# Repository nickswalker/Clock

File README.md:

Tock
====

An Arduino based nightstand alarm clock.

* Multiple alarms
* Accurate time with battery backup
* Configurable over Bluetooth Low Energy with [Tick](https://github.com/nickswalker/tick)

Independent Study Mentorship project for senior year at Communications Arts High School (2014).

### Hardware

The Tock is built around an Arduino-compatible board which is meant to be used in conjunction with a number
of cheap, widely available supporting modules. The PCB exposes all of the pins of the microcontroller, 
so it's easy to extend.

#### Bill of Materials

Part (Digi-Key #) | Quantity |
:---------------- | :-------:|
[Project PCB]()   | 1  
[HM-10 module](http://www.fasttech.com/products/0/10004051/1292002-ti-cc2540-bluetooth-40-ble-2540-transparent-serial) | 1
[Real time clock module]() | 1
[Adafruit I2C 4 digit seven segment display]() | 1
[Photoresistor]() | 1
[Female to male jumpers]() | 12
[Male header]()   | 2 rows of 40
[Female header]() | 1 row of 40
              | 1

### Firmware

The C++ Arduino sketch uses three main global singletons to manage the hardware; an `IOHandler`, a 
`TimeKeeper` and `SensorHandler`. Hardware extensions should be coupled with additional methods on
these objects. Another singleton, the `AlarmsManager`, handles the interpretation of time events. A 
`Settings` class exposes methods to manipulate the EPROM for storing information between power cycles.

Various subclasses of the abstract `Command` class encapsulate the interpretation and execution of
commands recieved over the UART line from the Bluetooth Low Energy module. The `Command` class itself
contains a factory method for producing its concrete subclasses. Each of these has full access to the 
global singletons and can manipulate the state of the clock.

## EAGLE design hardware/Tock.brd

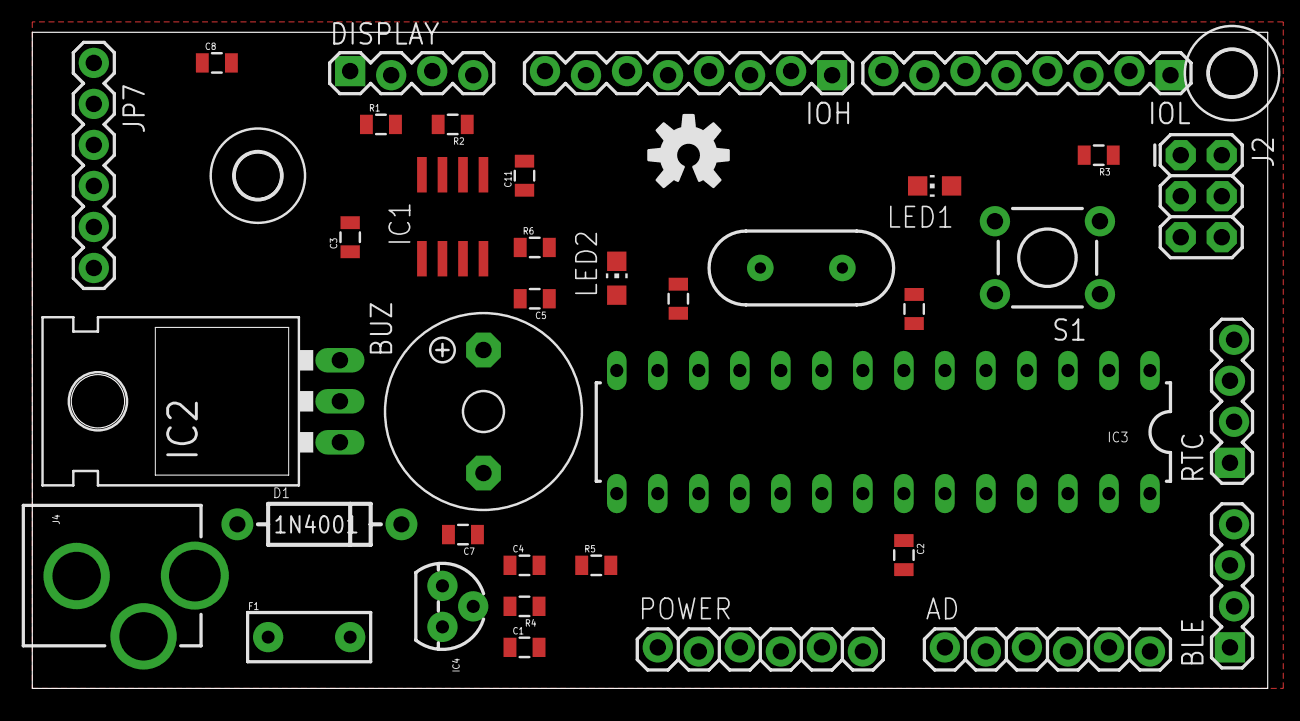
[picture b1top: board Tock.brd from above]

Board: 2 copper layers, 76.5 x 40.6 mm, 40 parts (0 on the bottom side), 36 nets, no tracks yet.

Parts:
AD: 1X06_LOCK
BLE: 1X04_LOCK
BUZ: F/TMB
C1, C4: 10uf; 0805
C2, C3, C5, C7, C8: 0.1uF; 0805
C9, C10: 22pF; 0805
C11: 220uf; 0805
D1: 1N4001; DIODE-1N4001
DISPLAY: 1X04_LOCK
F1: PTCPTH; PTC
IC1: NE555D; SO08
IC2: LM7805; TO-220-ALT
IC3: AVR-MEGA8-PPTH; DIL28-3
IC4: MCP1700-33; TO-92
IOH: 1X08_LOCK
IOL: 1X08_LOCK
J2: ISP; 2X3
J4: VIN; POWER_JACK_PTH_LOCK
JP7: FTDI_BASICPTH; FTDI_BASIC
LED1: RED; CHIP-LED0805
LED2: GREEN; CHIP-LED0805
POWER: 1X06_LOCK
R1: 1K; 0805
R2: 600; 0805
R3, R4: 330; 0805
R5: 10k; 0805
R6: 10K; 0805
RTC: 1X04_LOCK
S1: RESET; TACTILE-PTH
U$7: OSHW-LOGOM; OSHW-LOGO-M
U$8, U$10: 2,8
Y1: 16MHz; HC49US

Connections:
3.3V: C7.1, IC4.3, POWER.2
5V: BLE.4, C3.2, C4.1, C5.1, DISPLAY.4, IC1.8, IC2.OUT, IC3.7, IC3.20, IC4.2, J2.2, JP7.VCC, POWER.3, R1.1, R4.2, R5.2, RTC.3
555RST: IC1.4, IC3.4, IOL.3, R6.2
AD0: AD.1, IC3.23
AD1: AD.2, IC3.24
AD2: AD.3, IC3.25
AD3: AD.4, IC3.26
AD4: AD.5, IC3.27
AD5: AD.6, IC3.28
AREF: C2.1, IC3.21, IOH.8
DTR: C8.1, JP7.DTR
GND: BLE.1, BUZ.-, C1.2, C2.2, C3.1, C4.2, C5.2, C7.2, C9.1, C10.1, C11.2, DISPLAY.3, IC1.1, IC2.GND, IC3.8, IC3.22, IC4.1, IOH.7, J2.6, J4.GND, J4.GNDBREAK, JP7.CTS, JP7.GND, LED1.C, LED2.C, POWER.4, POWER.5, R6.1, RTC.4, S1.1, S1.2
IO3: IC3.5, IOL.4
IO4: IC3.6, IOL.5
IO5: IC3.11, IOL.6
IO6: IC3.12, IOL.7
IO7: IC3.13, IOL.8
IO8: IC3.14, IOH.1
IO9: IC3.15, IOH.2
MISO: DISPLAY.1, IC3.18, IOH.5, J2.1, RTC.2
MOSI: DISPLAY.2, IC3.17, IOH.4, J2.4, RTC.1
unnamed: LED1.A, R3.2
unnamed: LED2.A, R4.1
unnamed: C9.2, IC3.9, Y1.2
unnamed: C10.2, IC3.10, Y1.1
unnamed: C11.1, IC1.2, IC1.6, R2.1
unnamed: D1.A, F1.P$2
unnamed: BUZ.+, IC1.3
unnamed: IC1.7, R1.2, R2.2
RAW: F1.P$1, J4.PWR
RESET: C8.2, IC3.1, J2.5, POWER.1, R5.1, S1.3, S1.4
RX-I: BLE.2, IC3.2, IOL.1, JP7.TXO
SCK: IC3.19, IOH.6, J2.3, R3.1
SS: IC3.16, IOH.3
TX-O: BLE.3, IC3.3, IOL.2, JP7.RXI
VIN: C1.1, D1.C, IC2.IN, POWER.6

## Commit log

2013-11-30 Initial Commit
    Basic, incomplete outline
2014-01-06 Implement core display functionality
    Implement settings
    Implement seven segment driving
    Add fake constructers to get around lack of ‘new’ operator
2014-02-08 Add default time
    Add mood light color methods
    Add more verbose logging
2014-02-24 Refactor time display
    Move display formatting all into IO object
2014-02-25 Fix time display bug
    More explicit zeros added when needed
2014-02-26 Fix time zero padding
    It actually works now
2014-03-02 Rejigger time display method
    Switch to some conditional digit writing. String to int method has too
    many edge cases.
2014-03-10 Add Snooze Button Input
2014-03-11 Start adding serial command infrastructure
    Add ability to set time and date with strings
2014-03-17 Add more BLE control logic
    Refactor Settings class around a single Options enum
    Make colon stay on when not in blink mode (was previously off at all
    times by mistake)
2014-03-30 Tidy up settings serial parsing
    Add comments about data transfer size limits
    Fix snooze button time interval (sort of)
2014-03-31 Add light color control to serial commands
2014-04-01 Rename project
2014-04-09 Serial communication improvements
    Works from straight bytes now.
2014-04-13 Massive code cleanup
    Split pin defines into their own include
    Add section headers to increase class readability
    Refactor bluetooth time sync
    Remove cruft, old methods
2014-04-13 Move protocol enums into definitions header Make constant formatting consistent
2014-04-28 Move debug statements into compile time if blocks
    Switch from byte to uint8_t for consistency
2014-04-28 Add foundation for alarms
    Add alarm manager object
    Add alarm model
    Rename TimeHandler to clarify role
2014-05-14 Switch to Piezo over button
    Drop some dead code
2014-05-18 Finish alarm implementation
    Move bit-packing into its own utility class
2014-05-19 Implement setting retrieval
2014-08-17 Add preliminary WIP eagle files
2014-08-17 Move firmware to it's own folder
2014-08-17 Add lightbar
2014-12-24 Massive firmware refactoring
    Rename sketch to Firmware to appease the Arduino IDE
    Rename Alarm to AlarmT because Alarm is a reserved word
    Move enum definitions out of the pin definitions file
    Move responsibility for keeping track of alarm memory addresses to the
    Settings class
    Rename BitPacking class to BitManipulation for clarity
2015-01-02 Update hardware
    Remove extra bit-packing code and switch to standard library macros
    Encapsulate enums
    Add WIP BOM and more information to readme
    Finish routing hardware
    Switch to SMD capacitors and resistors
2015-01-23 Shrink board footprint further
2015-01-25 Integrate with latest Tick app
    Fix 555 timer sub circuit control pin
    Fix GetSetting command message
    Fix out of sync enum values
2015-02-01 Fix an issue with the colon blink setting
2015-02-01 Fix GetAlarmCommand
    Add unit tests

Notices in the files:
parts and their libraries:
SparkFun-Connectors: Licensing: Creative Commons ShareAlike 4.0 International - https://creativecommons.org/licenses/by-sa/4.0
